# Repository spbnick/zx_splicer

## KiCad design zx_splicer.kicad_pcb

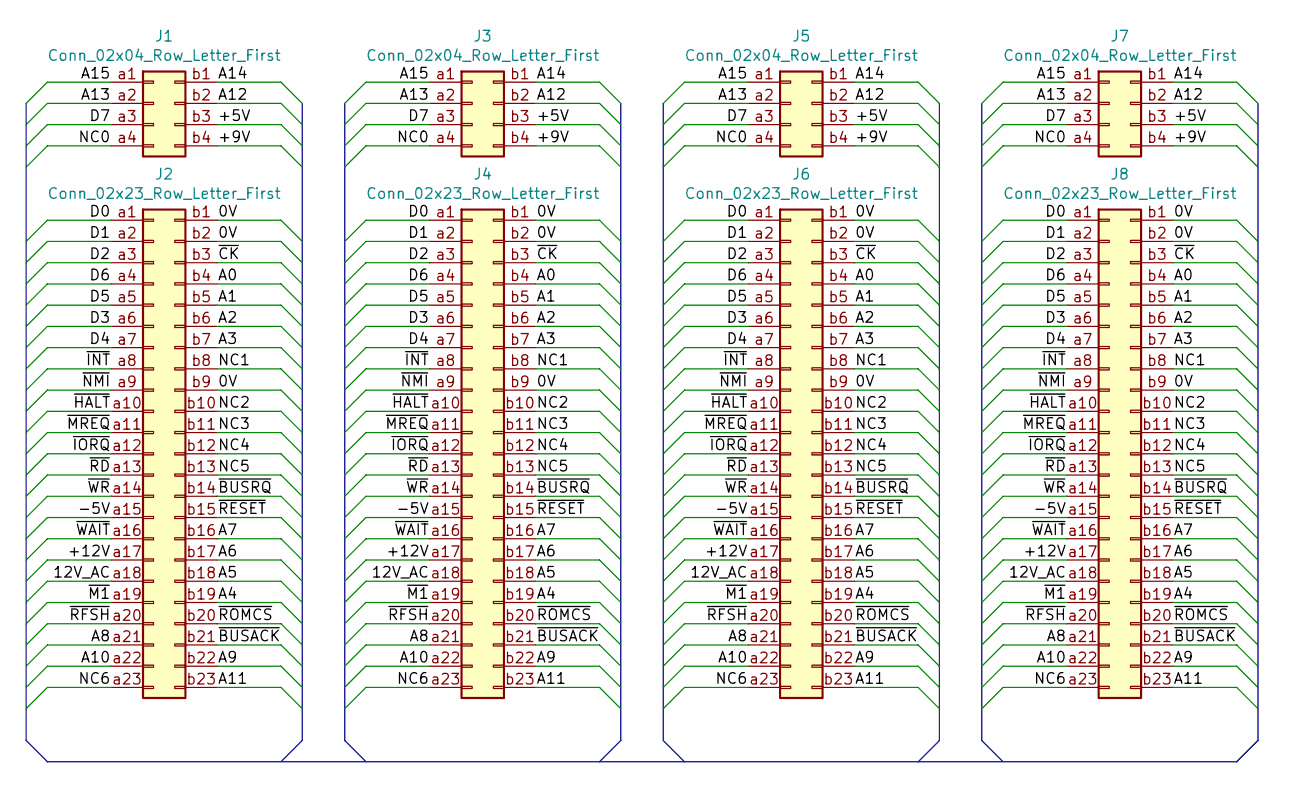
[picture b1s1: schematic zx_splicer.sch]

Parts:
J1: Conn_02x04_Row_Letter_First; short_board_socket
J2: Conn_02x23_Row_Letter_First; long_board_socket
J3: Conn_02x04_Row_Letter_First; short_pin_header
J4: Conn_02x23_Row_Letter_First; long_pin_header
J5: Conn_02x04_Row_Letter_First; short_pin_socket
J6: Conn_02x23_Row_Letter_First; long_pin_socket
J7: Conn_02x04_Row_Letter_First; short_board_edge
J8: Conn_02x23_Row_Letter_First; long_board_edge

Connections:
/0V: J2.b1, J2.b2, J2.b9, J4.b1, J4.b2, J4.b9, J6.b1, J6.b2, J6.b9, J8.b1, J8.b2, J8.b9
/12V_AC: J2.a18, J4.a18, J6.a18, J8.a18
/+5V: J1.b3, J3.b3, J5.b3, J7.b3
/+9V: J1.b4, J3.b4, J5.b4, J7.b4
/+12V: J2.a17, J4.a17, J6.a17, J8.a17
/-5V: J2.a15, J4.a15, J6.a15, J8.a15
/A0: J2.b4, J4.b4, J6.b4, J8.b4
/A1: J2.b5, J4.b5, J6.b5, J8.b5
/A2: J2.b6, J4.b6, J6.b6, J8.b6
/A3: J2.b7, J4.b7, J6.b7, J8.b7
/A4: J2.b19, J4.b19, J6.b19, J8.b19
/A5: J2.b18, J4.b18, J6.b18, J8.b18
/A6: J2.b17, J4.b17, J6.b17, J8.b17
/A7: J2.b16, J4.b16, J6.b16, J8.b16
/A8: J2.a21, J4.a21, J6.a21, J8.a21
/A9: J2.b22, J4.b22, J6.b22, J8.b22
/A10: J2.a22, J4.a22, J6.a22, J8.a22
/A11: J2.b23, J4.b23, J6.b23, J8.b23
/A12: J1.b2, J3.b2, J5.b2, J7.b2
/A13: J1.a2, J3.a2, J5.a2, J7.a2
/A14: J1.b1, J3.b1, J5.b1, J7.b1
/A15: J1.a1, J3.a1, J5.a1, J7.a1
/D0: J2.a1, J4.a1, J6.a1, J8.a1
/D1: J2.a2, J4.a2, J6.a2, J8.a2
/D2: J2.a3, J4.a3, J6.a3, J8.a3
/D3: J2.a6, J4.a6, J6.a6, J8.a6
/D4: J2.a7, J4.a7, J6.a7, J8.a7
/D5: J2.a5, J4.a5, J6.a5, J8.a5
/D6: J2.a4, J4.a4, J6.a4, J8.a4
/D7: J1.a3, J3.a3, J5.a3, J7.a3
/NC0: J1.a4, J3.a4, J5.a4, J7.a4
/NC1: J2.b8, J4.b8, J6.b8, J8.b8
/NC2: J2.b10, J4.b10, J6.b10, J8.b10
/NC3: J2.b11, J4.b11, J6.b11, J8.b11
/NC4: J2.b12, J4.b12, J6.b12, J8.b12
/NC5: J2.b13, J4.b13, J6.b13, J8.b13
/NC6: J2.a23, J4.a23, J6.a23, J8.a23
/~BUSACK: J2.b21, J4.b21, J6.b21, J8.b21
/~BUSRQ: J2.b14, J4.b14, J6.b14, J8.b14
/~CK: J2.b3, J4.b3, J6.b3, J8.b3
/~HALT: J2.a10, J4.a10, J6.a10, J8.a10
/~INT: J2.a8, J4.a8, J6.a8, J8.a8
/~IORQ: J2.a12, J4.a12, J6.a12, J8.a12
/~M1: J2.a19, J4.a19, J6.a19, J8.a19
/~MREQ: J2.a11, J4.a11, J6.a11, J8.a11
/~NMI: J2.a9, J4.a9, J6.a9, J8.a9
/~RD: J2.a13, J4.a13, J6.a13, J8.a13
/~RESET: J2.b15, J4.b15, J6.b15, J8.b15
/~RFSH: J2.a20, J4.a20, J6.a20, J8.a20
/~ROMCS: J2.b20, J4.b20, J6.b20, J8.b20
/~WAIT: J2.a16, J4.a16, J6.a16, J8.a16
/~WR: J2.a14, J4.a14, J6.a14, J8.a14

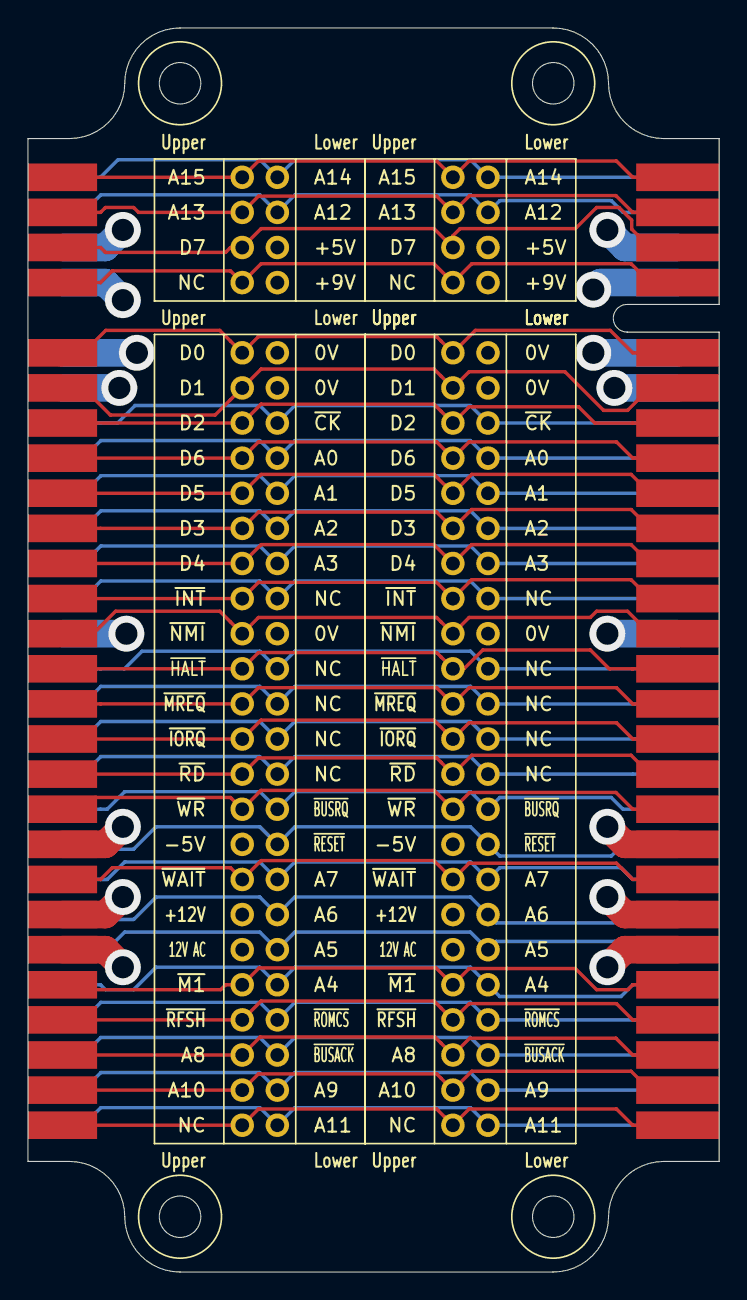
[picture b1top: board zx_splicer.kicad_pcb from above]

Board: 4 copper layers, 50.0 x 90.0 mm, 8 parts (0 on the bottom side), 52 nets.

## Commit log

2019-11-24 Add first routable but not solderable prototype
2019-11-24 Rename to ZX Splicer
2019-11-29 PCB power and ground on inner layers
2019-11-29 Route all connections
2019-11-29 Remove JLCPCB silkscreen text placeholder
2019-11-29 Add "gerbers" to .gitignore
